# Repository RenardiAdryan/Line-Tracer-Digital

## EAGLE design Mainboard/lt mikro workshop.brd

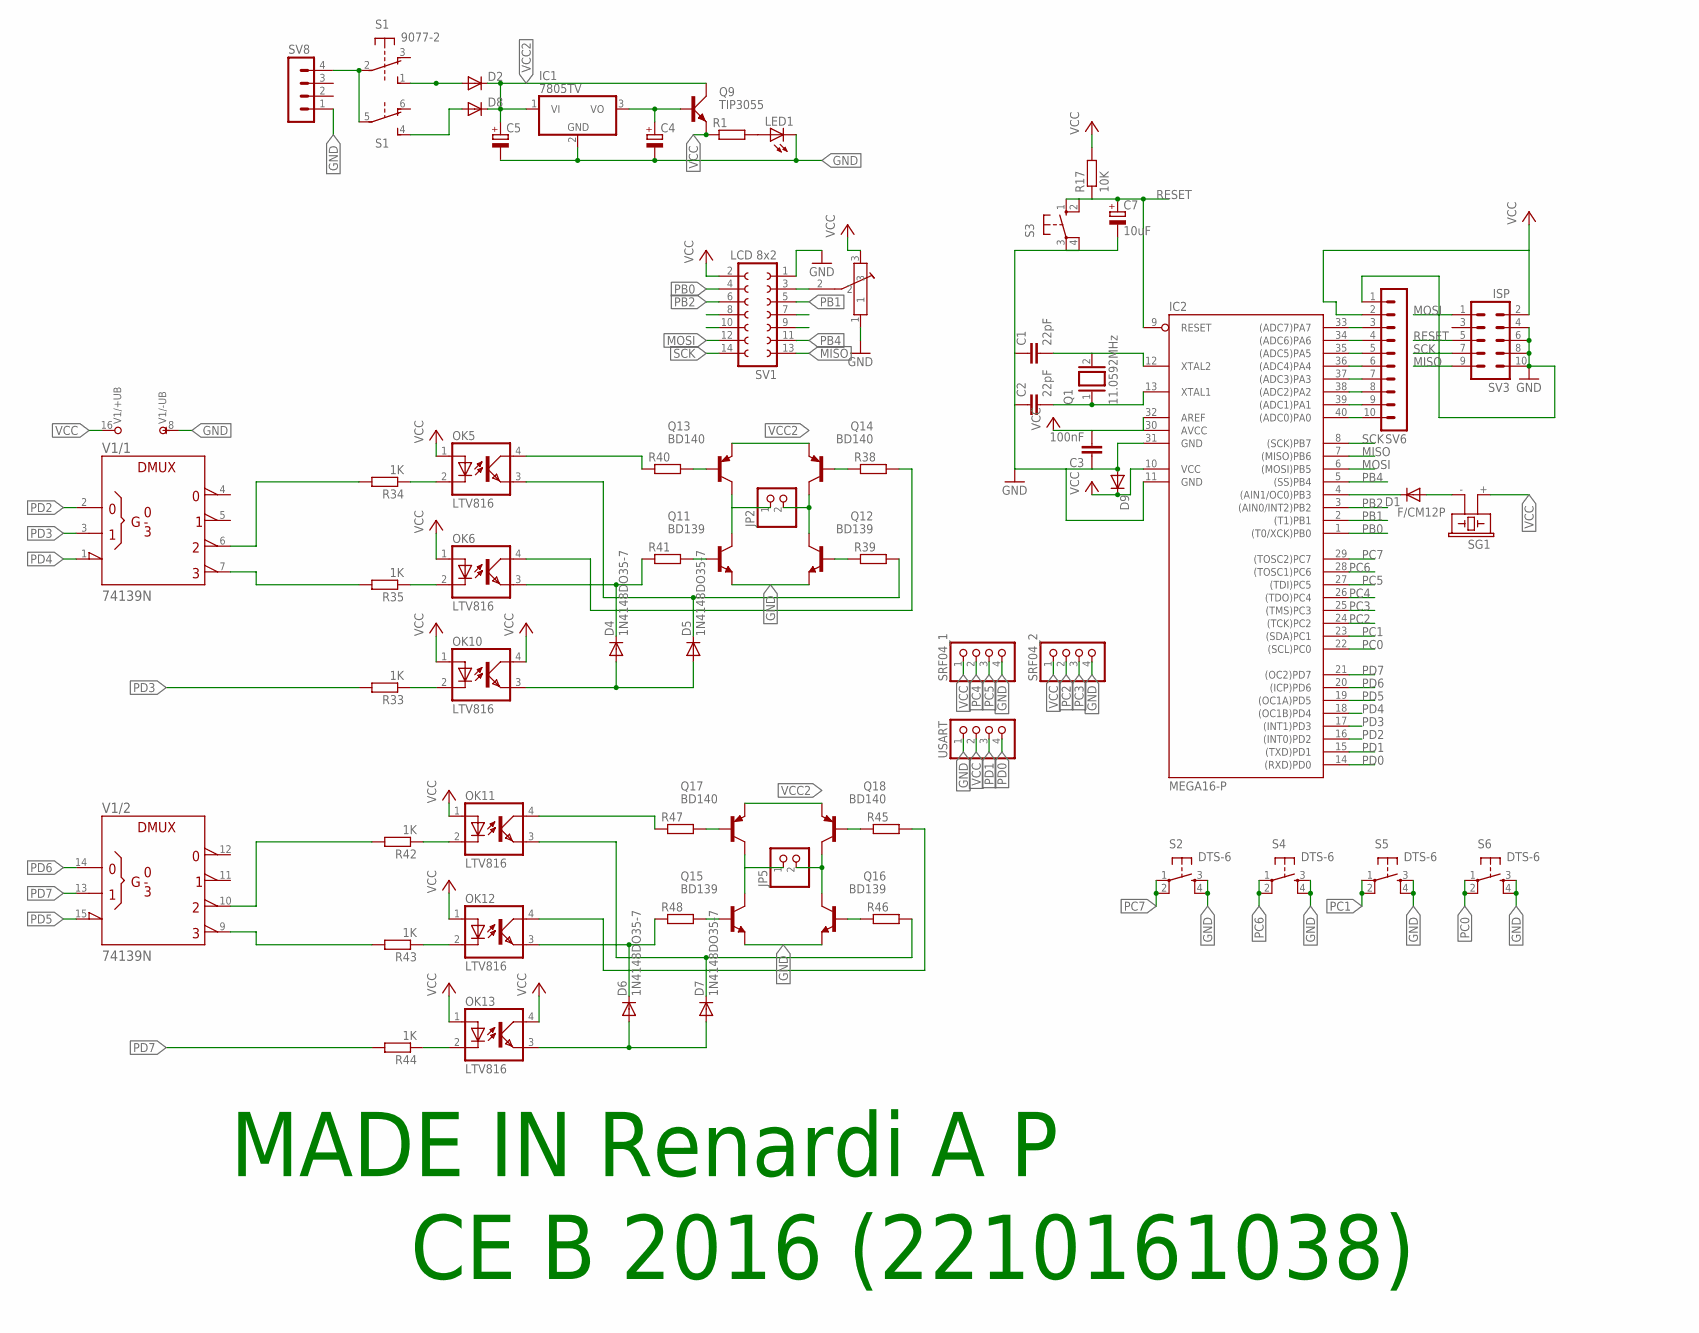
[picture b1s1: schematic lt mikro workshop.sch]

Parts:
C1, C2: 22pF; C2.5-2
C3: 100nF; C2.5-2
C4, C5: CPOL-EUE3.5-10; E3,5-10
C7: 10uF; E2-5
D1, D2, D8, D9: DIODE-DO214AA; DO214AA
D4, D5, D6, D7: 1N4148DO35-7; DO35-7
IC1: 7805TV; TO220V
IC2: MEGA16-P; DIL40
JP2, JP5: PINHD-1X2; 1X02
LED1: LED3MM
OK5, OK6, OK10, OK11, OK12, OK13: LTV816; DIL04
Q1: 11.0592MHz; QS
Q9: TIP3055; TOP3AV
Q11, Q12, Q15, Q16: BD139; TO126
Q13, Q14, Q17, Q18: BD140; TO126
R1, R38, R39, R40, R41, R45, R46, R47, R48: R-EU_0207/7; 0207/7
R17: 10K; 0204/7
R33, R34, R35, R42, R43, R44: 1K; 0204/7
S1: 9077-2
S2, S4, S5, S6: DTS-6
S3: 10-XX; B3F-10XX
SG1: F/CM12P
SRF04_1, SRF04_2: PINHD-1X4; 1X04
SV1: LCD 8x2; FE07-2
SV3: ISP; MA05-2
SV6: MA10-1
SV8: MA04-1
U$1: TRIMPOT
USART: PINHD-1X4; 1X04
V1: 74139N; DIL16

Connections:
GND: C1.1, C2.1, C3.1, C4.-, C5.-, C7.-, D9.A, IC1.2 (GND), IC2.11 (GND), IC2.31 (GND), LED1.K (C), Q11.1 (E), Q12.1 (E), Q15.1 (E), Q16.1 (E), S2.3, S2.4, S3.3, S3.4 (P1), S4.3, S4.4, S5.3, S5.4, S6.3, S6.4, SRF04_1.4, SRF04_2.4, SV1.1, SV3.4, SV3.6, SV3.8, SV3.10, SV6.1, SV8.1, U$1.1, USART.1, V1.8 (-UB)
MISO: IC2.7 ((MISO)PB6), SV1.13, SV3.9
MOSI: IC2.6 ((MOSI)PB5), SV1.12, SV3.1
unnamed: LED1.A, R1.2
unnamed: D8.A, S1.4 (S)
unnamed: D1.C, IC2.4 ((AIN1/OC0)PB3)
unnamed: C2.2, IC2.13 (XTAL1), Q1.1
unnamed: C1.2, IC2.12 (XTAL2), Q1.2
unnamed: D2.A, S1.1 (S)
unnamed: OK10.2 (C), R33.1
unnamed: OK5.2 (C), R34.1
unnamed: OK6.2 (C), R35.1
unnamed: C4.+, IC1.3 (VO), Q9.B
unnamed: JP2.1, Q11.2 (C), Q13.2 (C)
unnamed: S1.2, S1.5, SV8.4
unnamed: JP2.2, Q12.2 (C), Q14.2 (C)
unnamed: Q13.3 (B), R40.2
unnamed: Q14.3 (B), R38.1
unnamed: Q12.3 (B), R39.1
unnamed: R35.2, V1.7 (Y3)
unnamed: R34.2, V1.6 (Y2)
unnamed: Q11.3 (B), R41.2
unnamed: IC2.40 ((ADC0)PA0), SV6.10
unnamed: IC2.33 ((ADC7)PA7), SV6.3
unnamed: IC2.34 ((ADC6)PA6), SV6.4
unnamed: IC2.35 ((ADC5)PA5), SV6.5
unnamed: IC2.36 ((ADC4)PA4), SV6.6
unnamed: IC2.37 ((ADC3)PA3), SV6.7
unnamed: D1.A, SG1.- (2)
unnamed: OK5.4 (COL), R40.1
unnamed: IC2.38 ((ADC2)PA2), SV6.8
unnamed: IC2.39 ((ADC1)PA1), SV6.9
unnamed: D5.C, OK5.3 (EMIT), R39.2
unnamed: OK6.4 (COL), R38.2
unnamed: D4.C, OK6.3 (EMIT), R41.1
unnamed: D4.A, D5.A, OK10.3 (EMIT)
unnamed: OK12.2 (C), R43.1
unnamed: OK11.2 (C), R42.1
unnamed: OK13.2 (C), R44.1
unnamed: R43.2, V1.9 (Y3)
unnamed: R42.2, V1.10 (Y2)
unnamed: JP5.1, Q15.2 (C), Q17.2 (C)
unnamed: JP5.2, Q16.2 (C), Q18.2 (C)
unnamed: Q17.3 (B), R47.2
unnamed: Q18.3 (B), R45.1
unnamed: Q16.3 (B), R46.1
unnamed: Q15.3 (B), R48.2
unnamed: OK11.4 (COL), R47.1
unnamed: D7.C, OK11.3 (EMIT), R46.2
unnamed: OK12.4 (COL), R45.2
unnamed: D6.C, OK12.3 (EMIT), R48.1
unnamed: D6.A, D7.A, OK13.3 (EMIT)
PB0: IC2.1 ((T0/XCK)PB0), SV1.3, SV1.4, U$1.2
PB1: IC2.2 ((T1)PB1), SV1.5
PB2: IC2.3 ((AIN0/INT2)PB2), SV1.6
PB4: IC2.5 ((SS)PB4), SV1.11
PC0: IC2.22 ((SCL)PC0), S6.1, S6.2
PC1: IC2.23 ((SDA)PC1), S5.1, S5.2
PC2: IC2.24 ((TCK)PC2), SRF04_2.2
PC3: IC2.25 ((TMS)PC3), SRF04_2.3
PC4: IC2.26 ((TDO)PC4), SRF04_1.2
PC5: IC2.27 ((TDI)PC5), SRF04_1.3
PC6: IC2.28 ((TOSC1)PC6), S4.1, S4.2
PC7: IC2.29 ((TOSC2)PC7), S2.1, S2.2
PD0: IC2.14 ((RXD)PD0), USART.4
PD1: IC2.15 ((TXD)PD1), USART.3
PD2: IC2.16 ((INT0)PD2), V1.2 (A)
PD3: IC2.17 ((INT1)PD3), R33.2, V1.3 (B)
PD4: IC2.18 ((OC1B)PD4), V1.1 (!G)
PD5: IC2.19 ((OC1A)PD5), V1.15 (!G)
PD6: IC2.20 ((ICP)PD6), V1.14 (A)
PD7: IC2.21 ((OC2)PD7), R44.2, V1.13 (B)
RESET: C7.+, IC2.9 (RESET), R17.1, S3.1 (S), S3.2 (S1), SV3.5
SCK: IC2.8 ((SCK)PB7), SV1.14, SV3.7
VCC: C3.2, D9.C, IC2.10 (VCC), IC2.30 (AVCC), IC2.32 (AREF), OK5.1 (A), OK6.1 (A), OK10.1 (A), OK10.4 (COL), OK11.1 (A), OK12.1 (A), OK13.1 (A), OK13.4 (COL), Q9.E, R1.1, R17.2, SG1.+ (1), SRF04_1.1, SRF04_2.1, SV1.2, SV3.2, SV6.2, U$1.3, USART.2, V1.16 (+UB)
VCC2: C5.+, D2.C, D8.C, IC1.1 (VI), Q9.C, Q13.1 (E), Q14.1 (E), Q17.1 (E), Q18.1 (E)

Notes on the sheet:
MADE IN Renardi A P
CE B 2016 (2210161038)

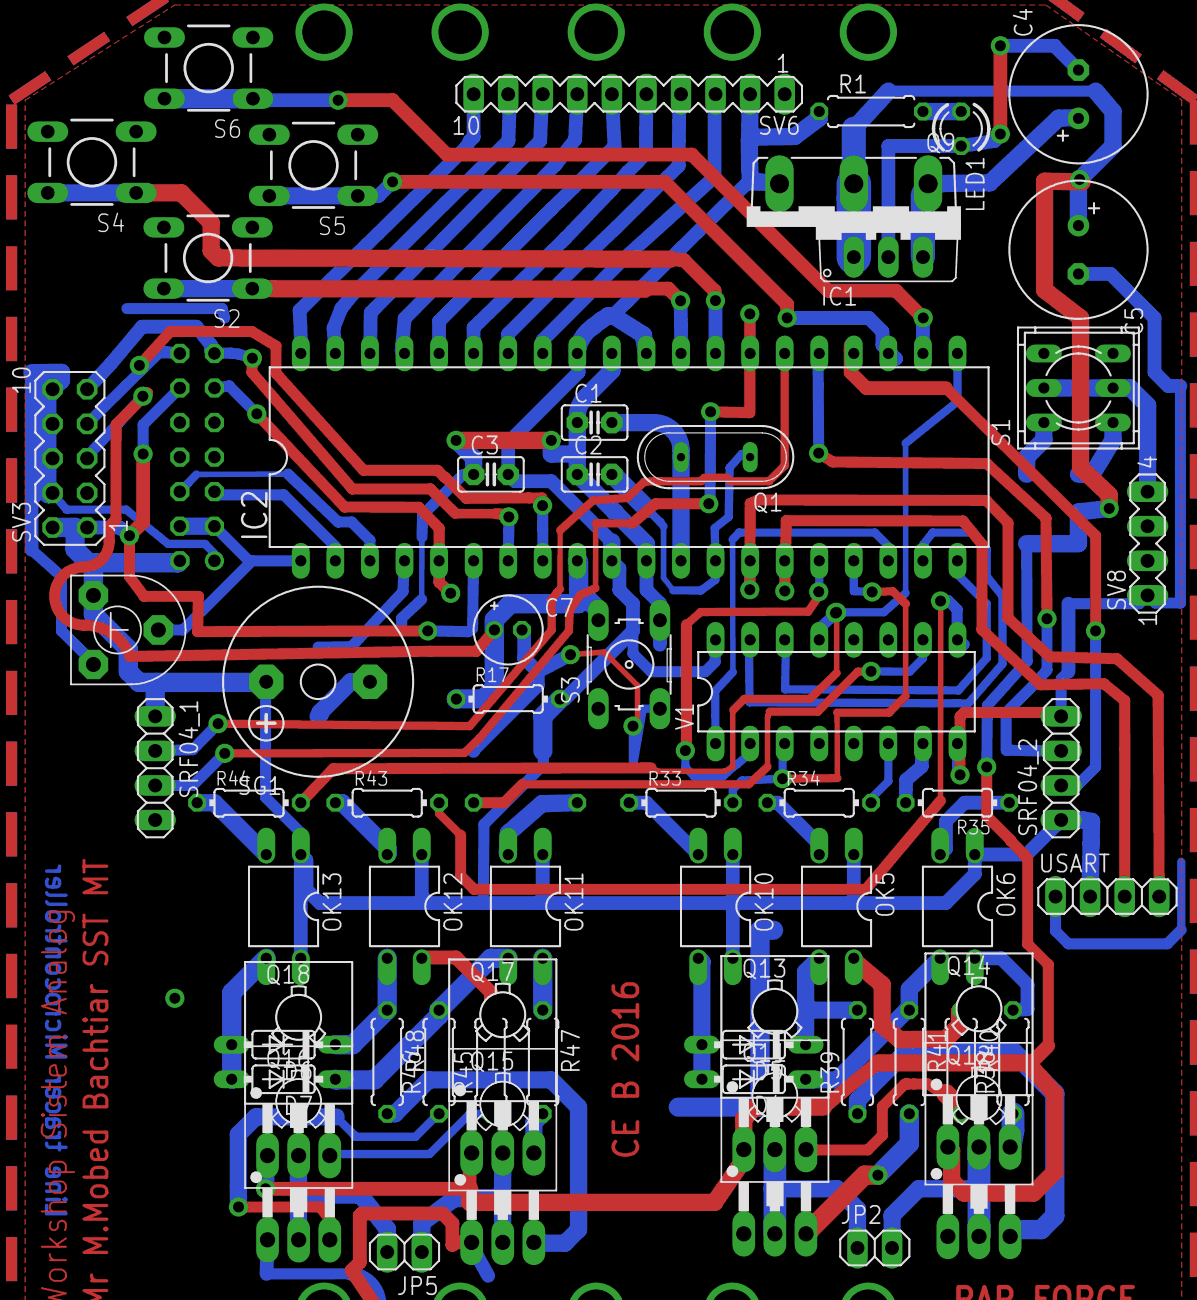
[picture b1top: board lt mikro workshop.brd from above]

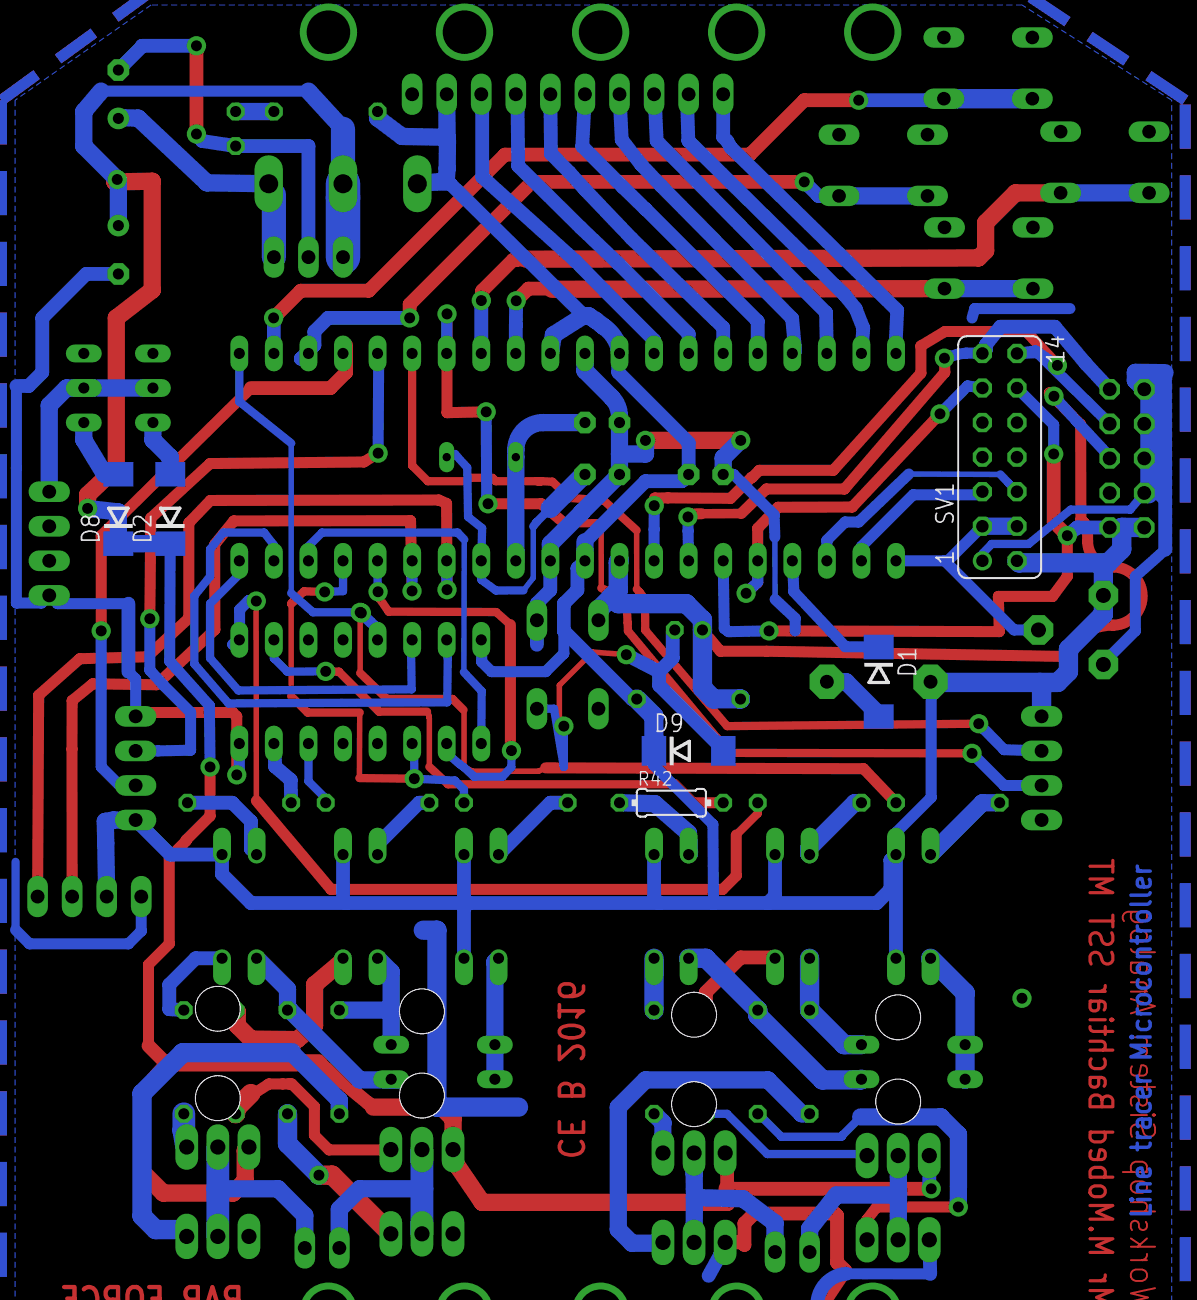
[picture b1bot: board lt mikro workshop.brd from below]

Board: 2 copper layers, 67 parts (6 on the bottom side), 76 nets.

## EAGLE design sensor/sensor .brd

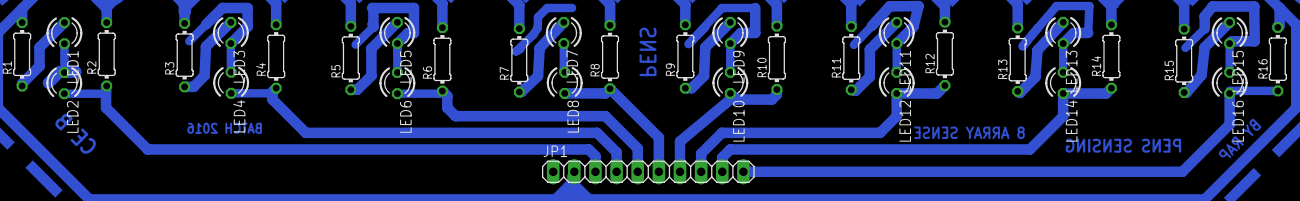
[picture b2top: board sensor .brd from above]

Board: 2 copper layers, 33 parts (0 on the bottom side), 18 nets.

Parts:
JP1: 1X10
LED1, LED2, LED3, LED4, LED5, LED6, LED7, LED8, LED9, LED10, LED11, LED12, LED13, LED14, LED15, LED16: LED3MM
R1, R3, R5, R7: 1K; 0204/7
R2, R8: 22K; 0204/7
R4, R6, R10, R12, R14, R16: 22k; 0204/7
R9, R11, R13, R15: 1k; 0204/7

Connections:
GND: JP1.1, LED1.K, LED2.A, LED3.K, LED4.A, LED5.K, LED6.A, LED7.K, LED8.A, LED9.K, LED10.A, LED11.K, LED12.A, LED13.K, LED14.A, LED15.K, LED16.A
unnamed: LED3.A, R3.1
unnamed: LED1.A, R1.1
unnamed: LED5.A, R5.1
unnamed: LED7.A, R7.1
unnamed: LED9.A, R9.1
unnamed: LED11.A, R11.1
unnamed: LED13.A, R13.1
unnamed: LED15.A, R15.1
OUT1: JP1.3, LED2.K, R2.1
OUT2: JP1.4, LED4.K, R4.1
OUT3: JP1.5, LED6.K, R6.1
OUT4: JP1.6, LED8.K, R8.1
OUT5: JP1.7, LED10.K, R10.1
OUT6: JP1.8, LED12.K, R12.1
OUT7: JP1.9, LED14.K, R14.1
OUT8: JP1.10, LED16.K, R16.1
VCC: JP1.2, R1.2, R2.2, R3.2, R4.2, R5.2, R6.2, R7.2, R8.2, R9.2, R10.2, R11.2, R12.2, R13.2, R14.2, R15.2, R16.2
